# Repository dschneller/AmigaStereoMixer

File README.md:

# AmigaStereoMixer

A simple circut to allow merging stereo input channels.

## What is it good for?
While the Commodore Amiga has great audio capabilities, normally their stereo output is not always enjoyable via headphones. This is because the Amiga outputs 4 voices, where 2 are mapped to each stereo channel. However, the left and right stereo channels are competely separated.  As long as the left and right speakers are close to each other (as in most TVs and
monitors of the time), this does not matter, because sound from both speakers reaches both ears.

When listening with headphones, though, there is no way for sound from the left channel to reach the right ear and vice versa. This often feels very unnatural, because, for example all percussion instruments might be on the right, while the melody is only getting to the left ear. 

This little board allows cross-fading the left and right channels to keep the separation, but have a little of each channel bleed over to the other side.

## How did it come about?

I [bought and refurbished an old Amiga 500](http://www.danielschneller.com/search/label/amiga) in December 2017.

Most of the time, I play games on it with headphones, because my modern monitor does not have built-in speakers and I did not want to clutter my desk with a pair of active external speakers. So I looked around to see if there were any readily available solutions first, but when I came across [Ms Mad Lemon's YouTube video](https://www.youtube.com/watch?v=cg2SPF7CMwM) about the same topic I thought it could be a fun first project to play with KiCad and create my first custom PCB.

## What does it look like?

The initial version was a little bigger and had a missing trace, making the adjustment knob do nothing, but that was easily fixed with a little piece of wire. So I designed a second revision, which is also quite a bit smaller, because the components are more densely packed. 

## How does it work?

There is two sets of input RCA jacks. The second one is completely optional and only there, because Ms Mad Lemon's had it, too. I just used the resistor and capacitor values she had already tried. I did, however, use bipolar caps instead of pairs of polarized ones back to back.
The left and right channels of both inputs get mixed together first. They then go through the variable resistor which decides how much of the left channel can bleed through to the right and vice versa.  

Finally, the mixed output goes to a TRS headphone jack.

Because this whole thing is completely passive, the output volume will be slightly reduced, compared to what you would get when connecting headphones directly. In my experience, though, it is not noticable.

## How to build it

Clone this repository and open the PCB file with KiCad. I created this with version 5.1, so use that least that. I assume, newer versions will be able to read this, too. 

### PCB

To get the PCB, you can upload either the KiCad PCB file directly to a manufacturer that supports it, or, if they don't, "plot" Gerber files for all the layers and drill holes with KiCad and then upload those. I won't go into the details, because there is a ton of documentation on that on the internet. 

### Components

For the capacitors, I chose Nichicon 47uF 16V 85°C. Make sure they are bipolar. The audio jacks for input (RCJ-012) and output (SJ1-3553NG) are from CUI Devices. The trimmer is a Bourns Inc. 3386F-1-102TLF. 10Ω resistors I had flying around from a resistor kit I bought a while ago. I ordered them everything from DigiKey, trying to get the cheapest options.

## Issues

* The trimmer I used is a linear 0-1㏀ model. While it works, audible changes in the amount of fading only happen in about the first 20% of a turn. Probably a variable resistor with a non-linear curve would yield better results. 

* I think I will change the 2nd pair of input jacks to an output. That way you could use a headphone or connect both channels through to some other output device. That's probably more useful than a second input to be mixed in with the Amiga sound.

## Disclaimer

This is a hobby project and I will not be responsible for any damage that might result from its use! I am neither an audio nor hardware specialist. While I tried to do my best and don't think it is very difficult to build, it is up to you to decide whether you want build one for yourself and dare to connect it to your devices :-)

## License

Licensed under the [CERN Open Hardware License v1.2](cern_ohl_v_1_2.txt).

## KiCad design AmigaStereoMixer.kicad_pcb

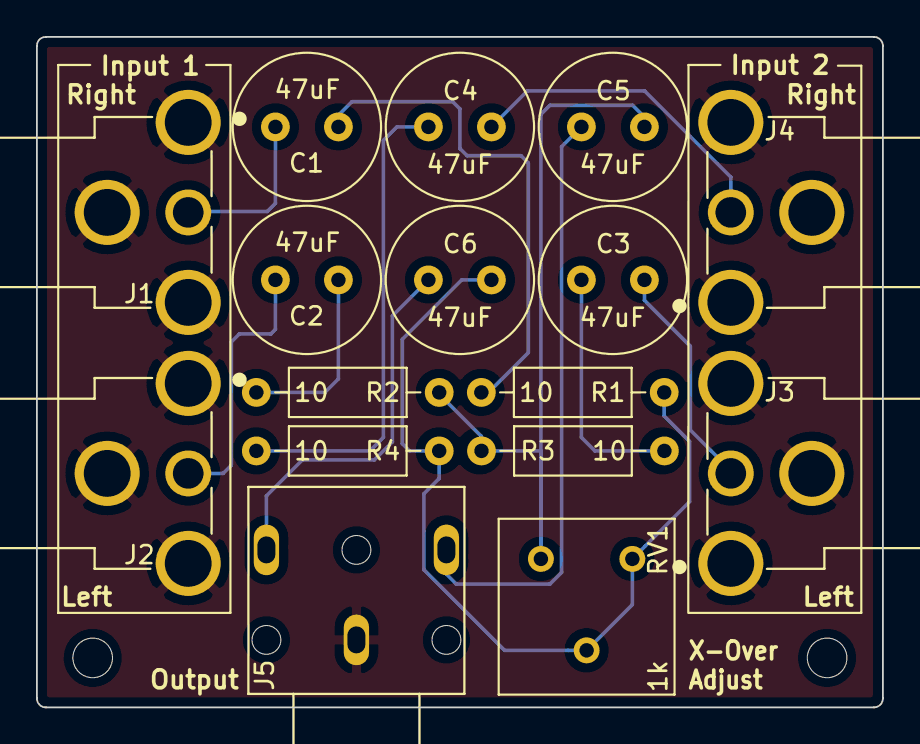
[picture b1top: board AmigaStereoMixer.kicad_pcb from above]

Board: 2 copper layers, 47.0 x 37.2 mm, 18 parts (0 on the bottom side), 13 nets.

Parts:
C1, C2, C3, C4, C5, C6: 47uF; C_Radial_D8.0mm_H11.5mm_P3.50mm
H1, H2: MountingHole; MountingHole_2.2mm_M2_DIN965
J1: IN1_R; CUI_RCJ-012
J2: IN1_L; CUI_RCJ-012
J3: IN2_L; CUI_RCJ-012
J4: IN2_R; CUI_RCJ-012
J5: OUT_TRS; CUI_SJ1-3553NG
R1, R2, R3, R4: 10; R_Axial_DIN0207_L6.3mm_D2.5mm_P10.16mm_Horizontal
RV1: 1k; Potentiometer_Bourns_3386F_Vertical

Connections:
GND: J1.1A, J1.1B, J1.1C, J2.1A, J2.1B, J2.1C, J3.1A, J3.1B, J3.1C, J4.1A, J4.1B, J4.1C, J5.1
unnamed: C1.1, R1.2
unnamed: C1.2, J1.2
unnamed: C2.1, R2.2
unnamed: C2.2, J2.2
unnamed: C3.1, R3.2
unnamed: C3.2, J3.2
unnamed: C4.1, R4.2
unnamed: C4.2, J4.2
unnamed: C5.1, J5.2
unnamed: C5.2, R2.1, R3.1, RV1.1
unnamed: C6.1, J5.3
unnamed: C6.2, R1.1, R4.1, RV1.2, RV1.3

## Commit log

2019-10-01 Arrange left & right groups more clearly in schema
2019-10-01 Add front GND plane
2019-10-01 Improve some trace routing
2019-10-01 Add mounting holes and an open hardware logo
2019-10-01 0.5mm traces, Left/Right labels moved
2019-10-01 Add v1 Board Rendering
2019-10-20 Rev 2: Add missing connection, route on back
    * Much more compact layout.
    * The variable resistor was missing a link to its
    pin 2, rendering it practically useless.
    * Update CUI symbols and footprints
    Use oval pad holes instead of board outline segments
    in SJ1-3553NG TRS output footprint.
2019-10-20 Sanitize symbol library
2019-10-20 Link license from readme

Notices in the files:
AmigaStereoMixer.kicad_pcb:
CERN Open Hardware Licence v1.2
